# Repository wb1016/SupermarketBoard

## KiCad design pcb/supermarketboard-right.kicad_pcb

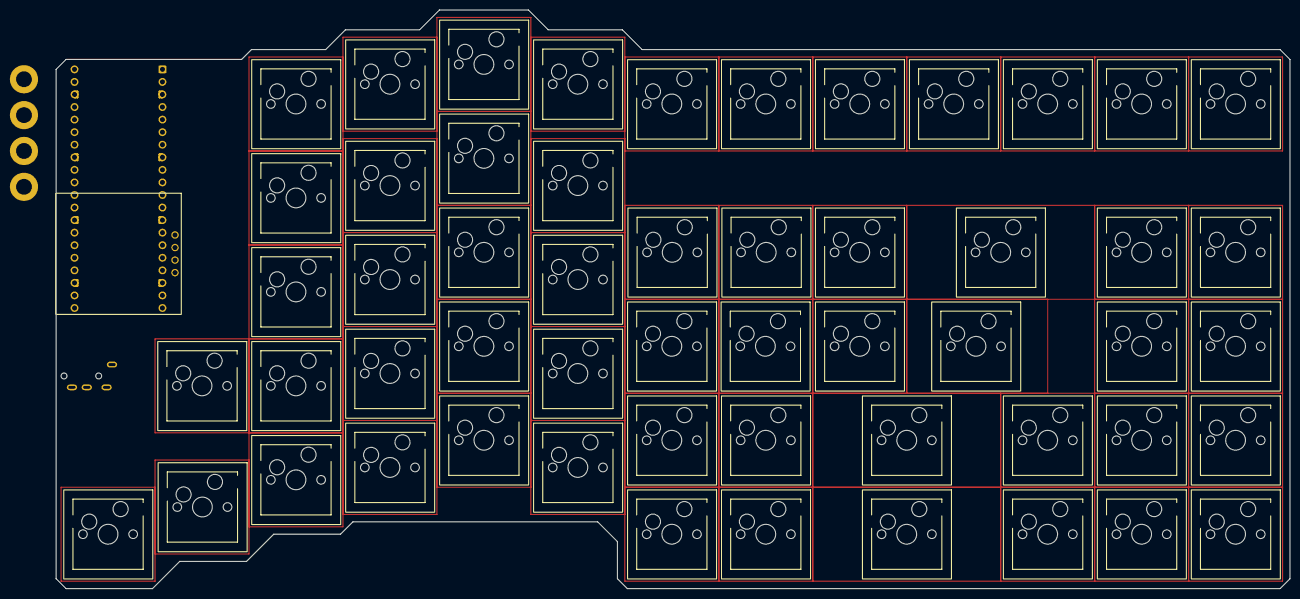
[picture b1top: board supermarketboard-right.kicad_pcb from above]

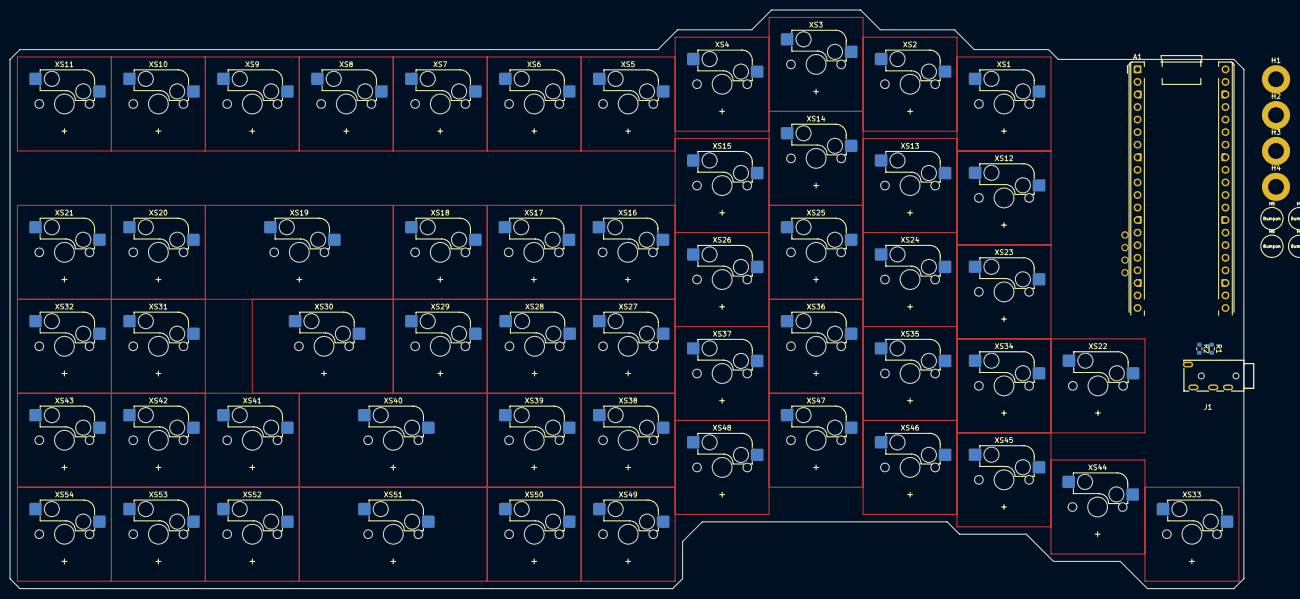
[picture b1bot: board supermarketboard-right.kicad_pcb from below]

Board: 2 copper layers, 249.5 x 117.0 mm, 70 parts (70 on the bottom side), 18 nets, no tracks yet.

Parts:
A1: RaspberryPi_Pico-OLED; RaspberryPi_Pico_THT-OLED
H1, H2, H3, H4: M3 Hole; MountingHole_3.2mm_M3_ISO7380_Pad
H5, H6, H7, H8, H9, H10, H11, H12: Bumpon; Bumpon-Mirror
J1: PJ-320A-4P DIP; AUDIO-TH_PJ-320A-4P-DIP
R1, R2: 3.9k; R_0603_1608Metric
XS1, XS2, XS3, XS4, XS5, XS6, XS7, XS8, XS9, XS10, XS11, XS12, XS13, XS14, XS15, XS16, XS17, XS18, XS19, XS20, XS21, XS22, XS23, XS24, XS25, XS26, XS27, XS28, XS29, XS30, XS31, XS32, XS33, XS34, XS35, XS36, XS37, XS38, XS39, XS40, XS41, XS42, XS43, XS44, XS45, XS46, XS47, XS48, XS49, XS50, XS51, XS52, XS53, XS54: CherryMX-HotSwap-NeoPixel; XS_Kailh_MX_1.00u-LEDpos

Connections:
+3.3V: A1.36 (3V3), A1.42 (OLED_VDD), R1.1, R2.1
COL1: A1.4 (GPIO2), XS1.1, XS22.1, XS33.1, XS44.1
COL2: A1.5 (GPIO3), XS2.1, XS12.1, XS23.1, XS34.1, XS45.1
COL3: A1.6 (GPIO4), XS3.1, XS13.1, XS24.1, XS35.1, XS46.1
COL4: A1.7 (GPIO5), XS4.1, XS14.1, XS25.1, XS36.1, XS47.1
COL5: A1.9 (GPIO6), XS5.1, XS15.1, XS26.1, XS37.1, XS48.1
COL6: A1.10 (GPIO7), XS6.1, XS16.1, XS27.1, XS38.1, XS49.1
COL7: A1.11 (GPIO8), XS7.1, XS17.1, XS28.1, XS39.1, XS50.1
COL8: A1.12 (GPIO9), XS8.1, XS18.1, XS29.1, XS40.1, XS51.1
COL9: A1.14 (GPIO10), XS9.1, XS19.1, XS30.1, XS41.1, XS52.1
COL10: A1.15 (GPIO11), XS10.1, XS20.1, XS31.1, XS42.1, XS53.1
COL11: A1.16 (GPIO12), XS11.1, XS21.1, XS32.1, XS43.1, XS54.1
GND: A1.3 (GND), A1.8 (GND), A1.13 (GND), A1.18 (GND), A1.23 (GND), A1.28 (GND), A1.33 (AGND), A1.38 (GND), A1.41 (OLED_GND), H1.1 (1_1), H2.1 (1_1), H3.1 (1_1), H4.1 (1_1), J1.A
OLED_SCL: A1.25 (GPIO19), A1.43 (OLED_SCL)
OLED_SDA: A1.24 (GPIO18), A1.44 (OLED_SDA)
SCL: A1.2 (GPIO1), J1.D, R2.2
SDA: A1.1 (GPIO0), J1.C, R1.2
VSYS: A1.39 (VSYS), J1.B

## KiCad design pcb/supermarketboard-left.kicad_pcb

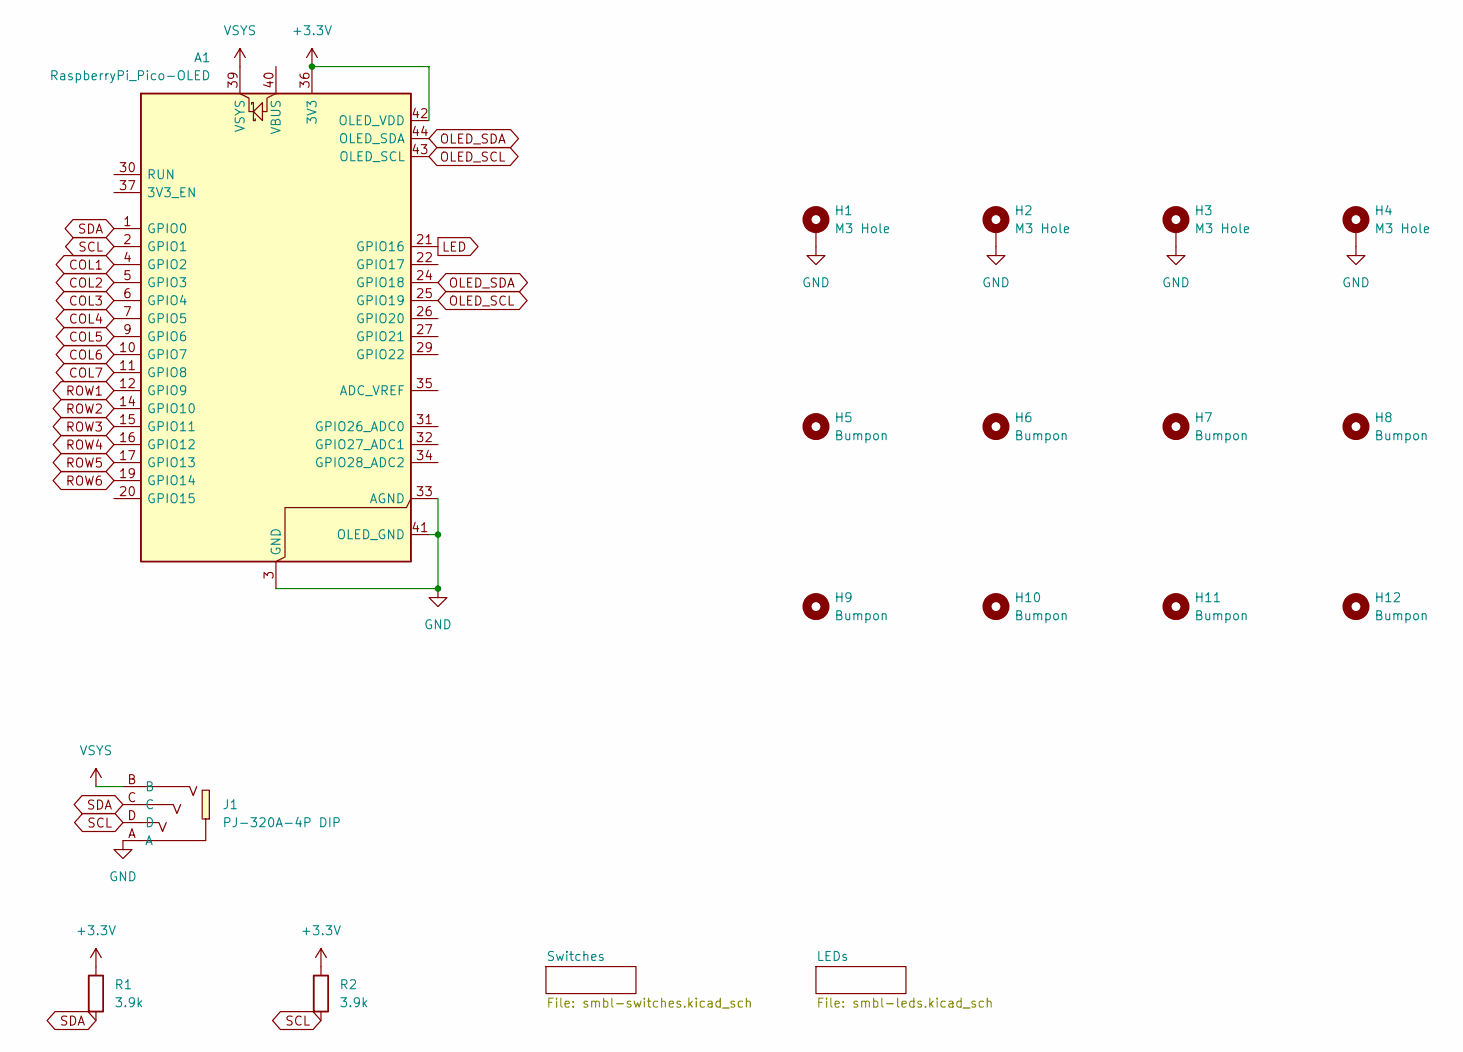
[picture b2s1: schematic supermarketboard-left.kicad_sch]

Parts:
A1: RaspberryPi_Pico-OLED; RaspberryPi_Pico_THT-OLED
H1, H2, H3, H4: M3 Hole; MountingHole_3.2mm_M3_ISO7380_Pad
H5, H6, H7, H8, H9, H10, H11, H12: Bumpon; Bumpon-Mirror
J1: PJ-320A-4P DIP; AUDIO-TH_PJ-320A-4P-DIP; LCSC Part C18185602
R1, R2: 3.9k; R_0603_1608Metric

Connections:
+3.3V: A1.36 (3V3), A1.42 (OLED_VDD), R1.1, R2.1
COL1: A1.4 (GPIO2); also elsewhere on the board
COL2: A1.5 (GPIO3); also elsewhere on the board
COL3: A1.6 (GPIO4); also elsewhere on the board
COL4: A1.7 (GPIO5); also elsewhere on the board
COL5: A1.9 (GPIO6); also elsewhere on the board
COL6: A1.10 (GPIO7); also elsewhere on the board
COL7: A1.11 (GPIO8); also elsewhere on the board
GND: A1.3 (GND), A1.8 (GND), A1.13 (GND), A1.18 (GND), A1.23 (GND), A1.28 (GND), A1.33 (AGND), A1.38 (GND), A1.41 (OLED_GND), H1.1 (1_1), H2.1 (1_1), H3.1 (1_1), H4.1 (1_1), J1.A; also elsewhere on the board
LED: A1.21 (GPIO16); also elsewhere on the board
OLED_SCL: A1.25 (GPIO19), A1.43 (OLED_SCL)
OLED_SDA: A1.24 (GPIO18), A1.44 (OLED_SDA)
ROW1: A1.12 (GPIO9); also elsewhere on the board
ROW2: A1.14 (GPIO10); also elsewhere on the board
ROW3: A1.15 (GPIO11); also elsewhere on the board
ROW4: A1.16 (GPIO12); also elsewhere on the board
ROW5: A1.17 (GPIO13); also elsewhere on the board
ROW6: A1.19 (GPIO14); also elsewhere on the board
SCL: A1.2 (GPIO1), J1.D, R2.2
SDA: A1.1 (GPIO0), J1.C, R1.2
VSYS: A1.39 (VSYS), J1.B

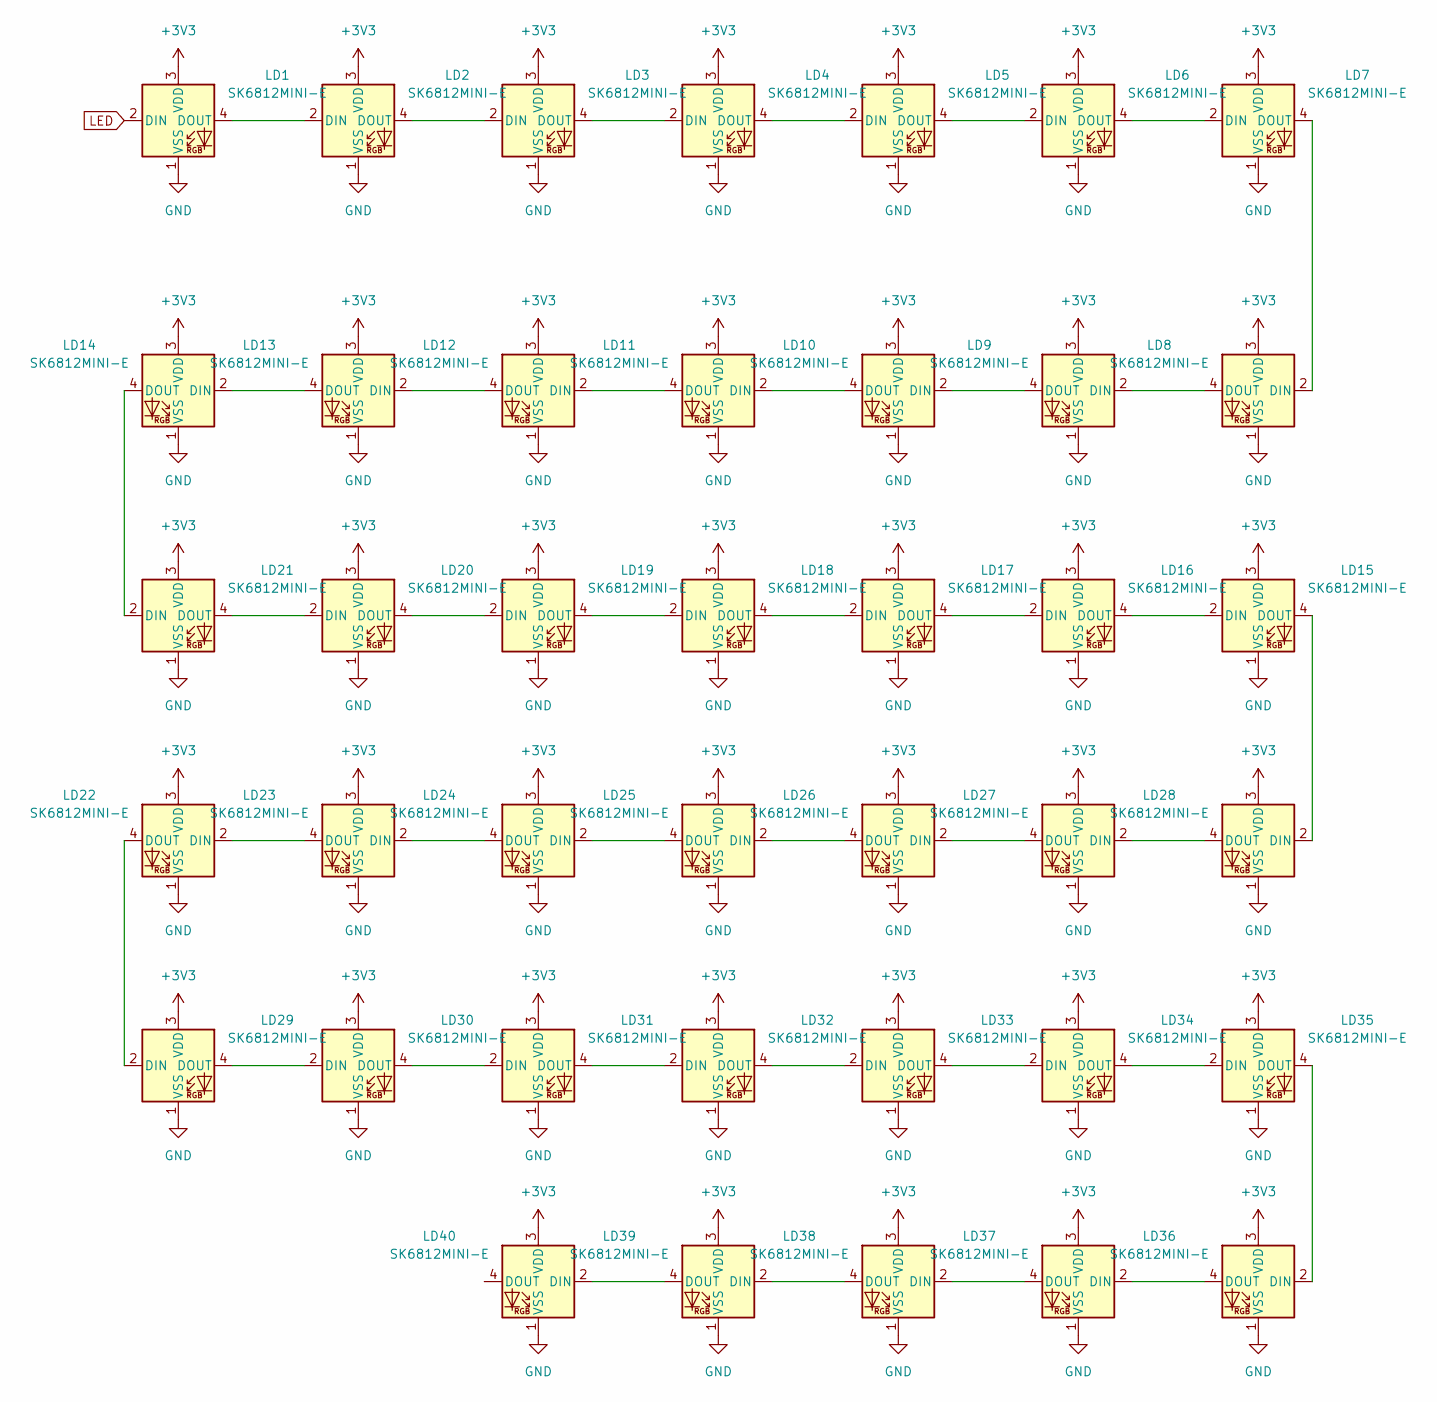
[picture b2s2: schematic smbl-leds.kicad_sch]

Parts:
LD1, LD2, LD3, LD4, LD5, LD6, LD7, LD8, LD9, LD10, LD11, LD12, LD13, LD14, LD15, LD16, LD17, LD18, LD19, LD20, LD21, LD22, LD23, LD24, LD25, LD26, LD27, LD28, LD29, LD30, LD31, LD32, LD33, LD34, LD35, LD36, LD37, LD38, LD39, LD40: SK6812MINI-E; LED_SK6812MINI-E_3.2x2.8mm_P1.5mm_ReverseMount

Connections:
+3V3: LD1.3 (VDD), LD2.3 (VDD), LD3.3 (VDD), LD4.3 (VDD), LD5.3 (VDD), LD6.3 (VDD), LD7.3 (VDD), LD8.3 (VDD), LD9.3 (VDD), LD10.3 (VDD), LD11.3 (VDD), LD12.3 (VDD), LD13.3 (VDD), LD14.3 (VDD), LD15.3 (VDD), LD16.3 (VDD), LD17.3 (VDD), LD18.3 (VDD), LD19.3 (VDD), LD20.3 (VDD), LD21.3 (VDD), LD22.3 (VDD), LD23.3 (VDD), LD24.3 (VDD), LD25.3 (VDD), LD26.3 (VDD), LD27.3 (VDD), LD28.3 (VDD), LD29.3 (VDD), LD30.3 (VDD), LD31.3 (VDD), LD32.3 (VDD), LD33.3 (VDD), LD34.3 (VDD), LD35.3 (VDD), LD36.3 (VDD), LD37.3 (VDD), LD38.3 (VDD), LD39.3 (VDD), LD40.3 (VDD)
GND: LD1.1 (VSS), LD2.1 (VSS), LD3.1 (VSS), LD4.1 (VSS), LD5.1 (VSS), LD6.1 (VSS), LD7.1 (VSS), LD8.1 (VSS), LD9.1 (VSS), LD10.1 (VSS), LD11.1 (VSS), LD12.1 (VSS), LD13.1 (VSS), LD14.1 (VSS), LD15.1 (VSS), LD16.1 (VSS), LD17.1 (VSS), LD18.1 (VSS), LD19.1 (VSS), LD20.1 (VSS), LD21.1 (VSS), LD22.1 (VSS), LD23.1 (VSS), LD24.1 (VSS), LD25.1 (VSS), LD26.1 (VSS), LD27.1 (VSS), LD28.1 (VSS), LD29.1 (VSS), LD30.1 (VSS), LD31.1 (VSS), LD32.1 (VSS), LD33.1 (VSS), LD34.1 (VSS), LD35.1 (VSS), LD36.1 (VSS), LD37.1 (VSS), LD38.1 (VSS), LD39.1 (VSS), LD40.1 (VSS); also elsewhere on the board
LED: LD1.2 (DIN); also elsewhere on the board
unnamed: LD1.4 (DOUT), LD2.2 (DIN)
unnamed: LD2.4 (DOUT), LD3.2 (DIN)
unnamed: LD3.4 (DOUT), LD4.2 (DIN)
unnamed: LD4.4 (DOUT), LD5.2 (DIN)
unnamed: LD5.4 (DOUT), LD6.2 (DIN)
unnamed: LD6.4 (DOUT), LD7.2 (DIN)
unnamed: LD7.4 (DOUT), LD8.2 (DIN)
unnamed: LD8.4 (DOUT), LD9.2 (DIN)
unnamed: LD9.4 (DOUT), LD10.2 (DIN)
unnamed: LD10.4 (DOUT), LD11.2 (DIN)
unnamed: LD11.4 (DOUT), LD12.2 (DIN)
unnamed: LD12.4 (DOUT), LD13.2 (DIN)
unnamed: LD13.4 (DOUT), LD14.2 (DIN)
unnamed: LD14.4 (DOUT), LD21.2 (DIN)
unnamed: LD15.2 (DIN), LD16.4 (DOUT)
unnamed: LD15.4 (DOUT), LD28.2 (DIN)
unnamed: LD16.2 (DIN), LD17.4 (DOUT)
unnamed: LD17.2 (DIN), LD18.4 (DOUT)
unnamed: LD18.2 (DIN), LD19.4 (DOUT)
unnamed: LD19.2 (DIN), LD20.4 (DOUT)
unnamed: LD20.2 (DIN), LD21.4 (DOUT)
unnamed: LD22.2 (DIN), LD23.4 (DOUT)
unnamed: LD22.4 (DOUT), LD29.2 (DIN)
unnamed: LD23.2 (DIN), LD24.4 (DOUT)
unnamed: LD24.2 (DIN), LD25.4 (DOUT)
unnamed: LD25.2 (DIN), LD26.4 (DOUT)
unnamed: LD26.2 (DIN), LD27.4 (DOUT)
unnamed: LD27.2 (DIN), LD28.4 (DOUT)
unnamed: LD29.4 (DOUT), LD30.2 (DIN)
unnamed: LD30.4 (DOUT), LD31.2 (DIN)
unnamed: LD31.4 (DOUT), LD32.2 (DIN)
unnamed: LD32.4 (DOUT), LD33.2 (DIN)
unnamed: LD33.4 (DOUT), LD34.2 (DIN)
unnamed: LD34.4 (DOUT), LD35.2 (DIN)
unnamed: LD35.4 (DOUT), LD36.2 (DIN)
unnamed: LD36.4 (DOUT), LD37.2 (DIN)
unnamed: LD37.4 (DOUT), LD38.2 (DIN)
unnamed: LD38.4 (DOUT), LD39.2 (DIN)
unnamed: LD39.4 (DOUT), LD40.2 (DIN)

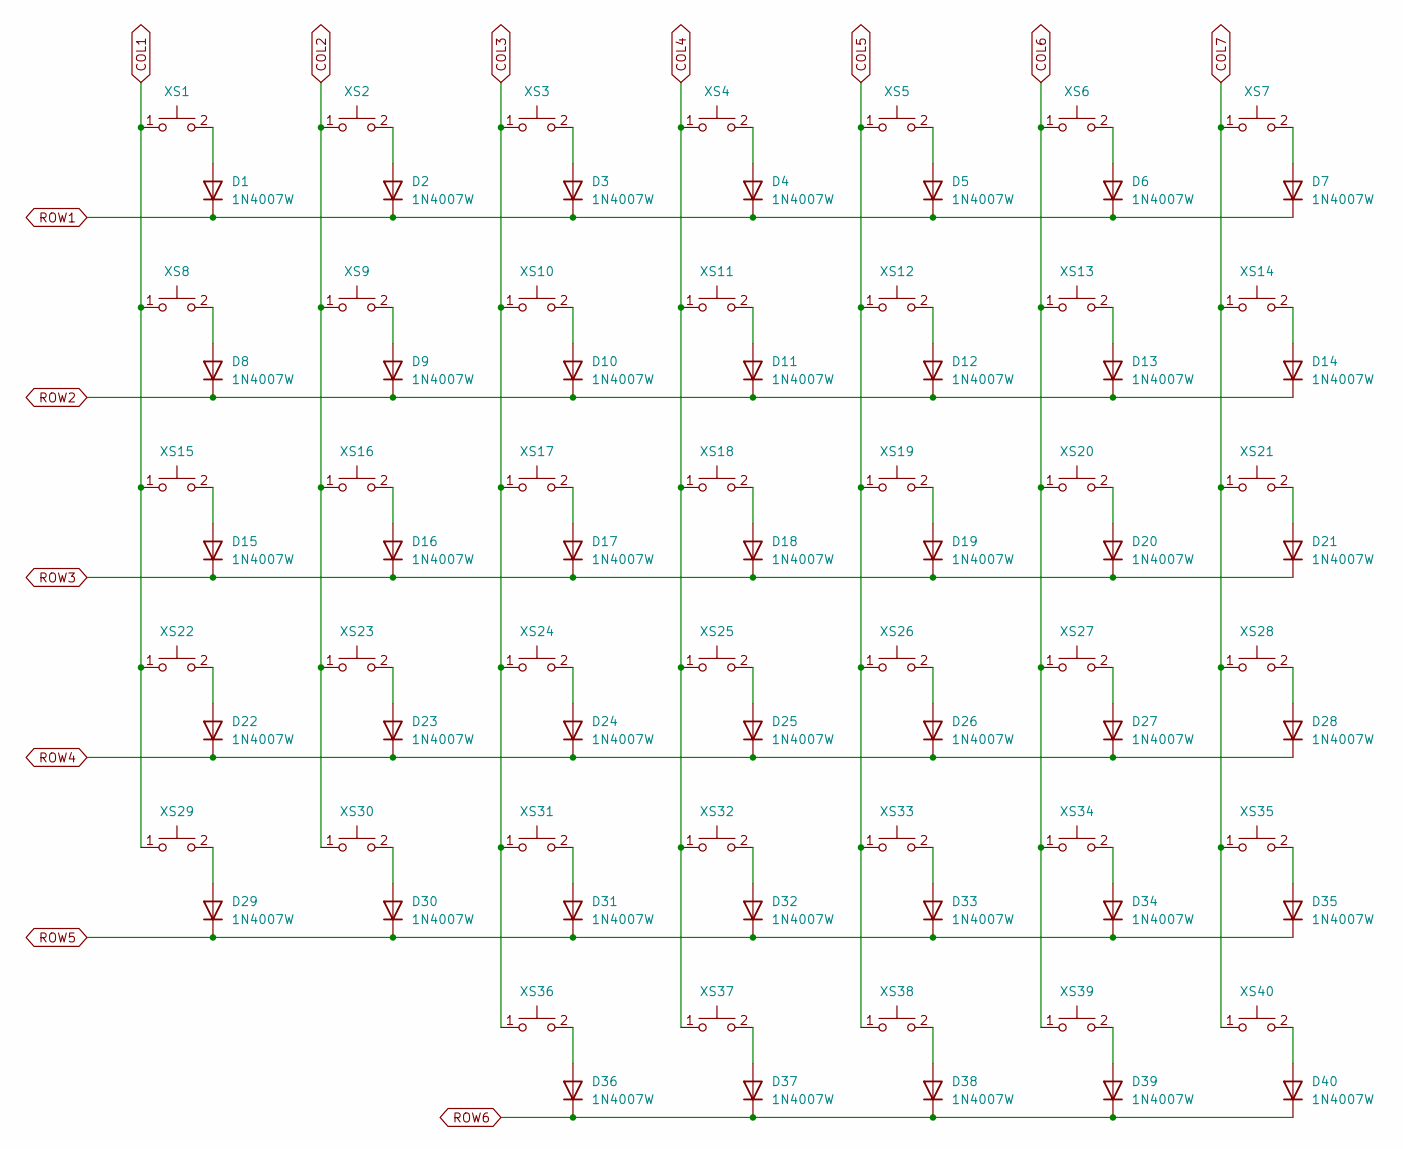
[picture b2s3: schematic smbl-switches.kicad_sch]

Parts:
D1, D2, D3, D4, D5, D6, D7, D8, D9, D10, D11, D12, D13, D14, D15, D16, D17, D18, D19, D20, D21, D22, D23, D24, D25, D26, D27, D28, D29, D30, D31, D32, D33, D34, D35, D36, D37, D38, D39, D40: 1N4007W; SOD-123FL_L2.7-W1.8-LS3.7-RD
XS1, XS2, XS3, XS4, XS5, XS6, XS7, XS8, XS9, XS10, XS11, XS12, XS13, XS14, XS16, XS17, XS18, XS19, XS20, XS21, XS22, XS23, XS24, XS25, XS26, XS27, XS28, XS30, XS31, XS32, XS33, XS34, XS35, XS36, XS37, XS38, XS39, XS40: CherryMX-HotSwap-NeoPixel; XS_Kailh_MX_1.00u-LEDpos
XS15: CherryMX-HotSwap-NeoPixel; XS_Kailh_MX_1.50u-LEDpos
XS29: CherryMX-HotSwap-NeoPixel; XS_Kailh_MX_2.00u-LEDpos

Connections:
COL1: XS1.1, XS8.1, XS15.1, XS22.1, XS29.1; also elsewhere on the board
COL2: XS2.1, XS9.1, XS16.1, XS23.1, XS30.1; also elsewhere on the board
COL3: XS3.1, XS10.1, XS17.1, XS24.1, XS31.1, XS36.1; also elsewhere on the board
COL4: XS4.1, XS11.1, XS18.1, XS25.1, XS32.1, XS37.1; also elsewhere on the board
COL5: XS5.1, XS12.1, XS19.1, XS26.1, XS33.1, XS38.1; also elsewhere on the board
COL6: XS6.1, XS13.1, XS20.1, XS27.1, XS34.1, XS39.1; also elsewhere on the board
COL7: XS7.1, XS14.1, XS21.1, XS28.1, XS35.1, XS40.1; also elsewhere on the board
unnamed: D1.2 (A), XS1.2
unnamed: D2.2 (A), XS2.2
unnamed: D3.2 (A), XS3.2
unnamed: D4.2 (A), XS4.2
unnamed: D5.2 (A), XS5.2
unnamed: D6.2 (A), XS6.2
unnamed: D7.2 (A), XS7.2
unnamed: D8.2 (A), XS8.2
unnamed: D9.2 (A), XS9.2
unnamed: D10.2 (A), XS10.2
unnamed: D11.2 (A), XS11.2
unnamed: D12.2 (A), XS12.2
unnamed: D13.2 (A), XS13.2
unnamed: D14.2 (A), XS14.2
unnamed: D15.2 (A), XS15.2
unnamed: D16.2 (A), XS16.2
unnamed: D17.2 (A), XS17.2
unnamed: D18.2 (A), XS18.2
unnamed: D19.2 (A), XS19.2
unnamed: D20.2 (A), XS20.2
unnamed: D21.2 (A), XS21.2
unnamed: D22.2 (A), XS22.2
unnamed: D23.2 (A), XS23.2
unnamed: D24.2 (A), XS24.2
unnamed: D25.2 (A), XS25.2
unnamed: D26.2 (A), XS26.2
unnamed: D27.2 (A), XS27.2
unnamed: D28.2 (A), XS28.2
unnamed: D29.2 (A), XS29.2
unnamed: D30.2 (A), XS30.2
unnamed: D31.2 (A), XS31.2
unnamed: D32.2 (A), XS32.2
unnamed: D33.2 (A), XS33.2
unnamed: D34.2 (A), XS34.2
unnamed: D35.2 (A), XS35.2
unnamed: D36.2 (A), XS36.2
unnamed: D37.2 (A), XS37.2
unnamed: D38.2 (A), XS38.2
unnamed: D39.2 (A), XS39.2
unnamed: D40.2 (A), XS40.2
ROW1: D1.1 (K), D2.1 (K), D3.1 (K), D4.1 (K), D5.1 (K), D6.1 (K), D7.1 (K); also elsewhere on the board
ROW2: D8.1 (K), D9.1 (K), D10.1 (K), D11.1 (K), D12.1 (K), D13.1 (K), D14.1 (K); also elsewhere on the board
ROW3: D15.1 (K), D16.1 (K), D17.1 (K), D18.1 (K), D19.1 (K), D20.1 (K), D21.1 (K); also elsewhere on the board
ROW4: D22.1 (K), D23.1 (K), D24.1 (K), D25.1 (K), D26.1 (K), D27.1 (K), D28.1 (K); also elsewhere on the board
ROW5: D29.1 (K), D30.1 (K), D31.1 (K), D32.1 (K), D33.1 (K), D34.1 (K), D35.1 (K); also elsewhere on the board
ROW6: D36.1 (K), D37.1 (K), D38.1 (K), D39.1 (K), D40.1 (K); also elsewhere on the board

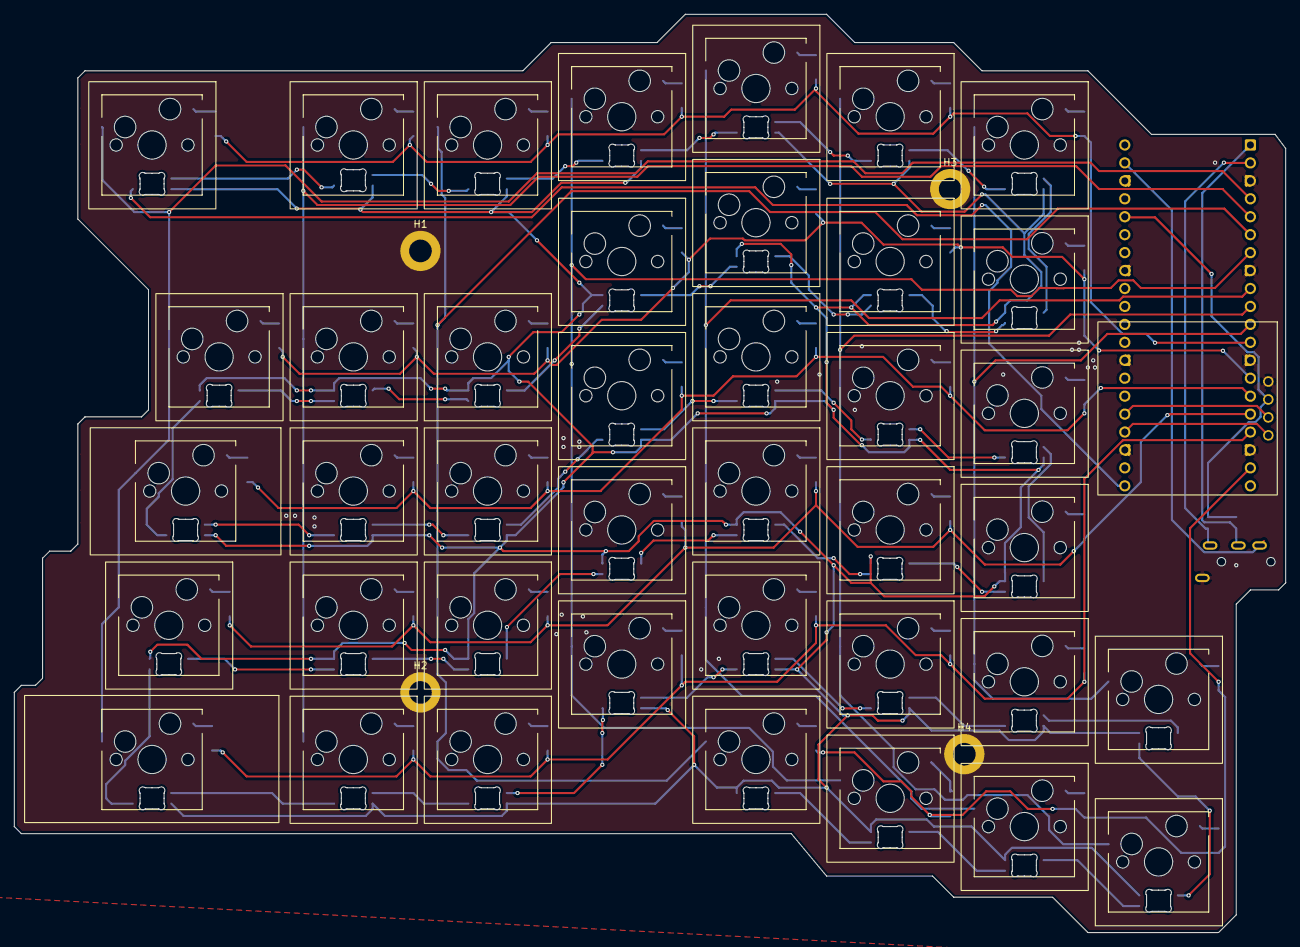
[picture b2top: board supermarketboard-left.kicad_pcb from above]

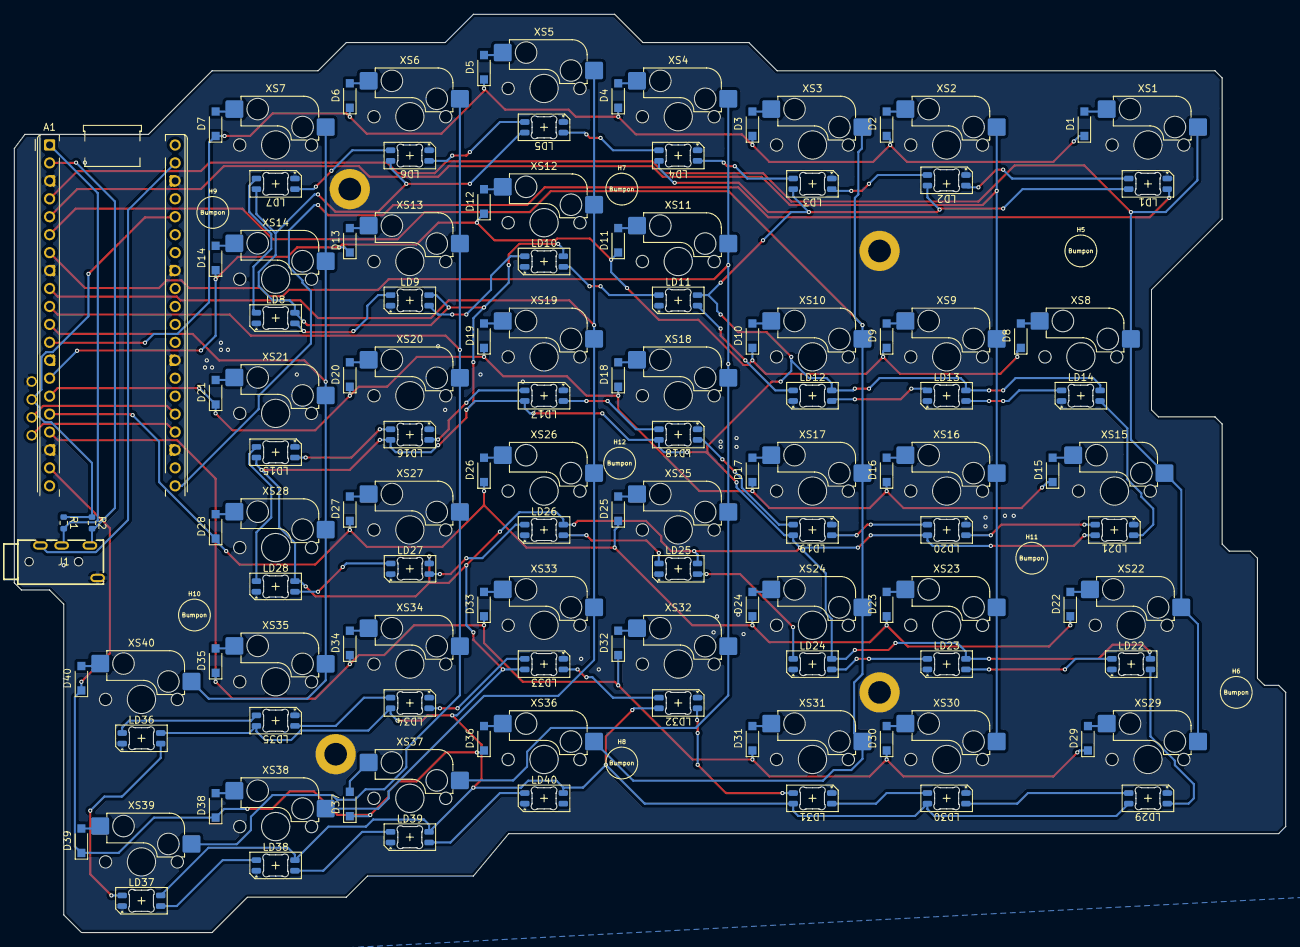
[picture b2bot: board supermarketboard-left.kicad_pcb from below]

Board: 2 copper layers, 179.9 x 129.9 mm, 136 parts (132 on the bottom side), 101 nets.

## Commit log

2026-05-06 asdflkadflkjahdfkjhafhjkl
2026-05-06 asdflkadflkjahdfkjhafhjklasdffadsf
2026-05-06 buiaohvcdfsabocfiudyabcf
2026-05-07 asdfhkjaksdfhjfasdjkhashkdfj
2026-05-07 xtsrdcdgtybhvgjvgbhjvbh
